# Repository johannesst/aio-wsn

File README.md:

# aio-wsn / FAIL
**Akustische Indoor-Ortung / Failed Audio Indoor Localisation**

Hard- und Softwareprojekt zur akustischen Ortung von Sensorknoten im Raum. Siehe dazu auch die [Projektpräsentation (PDF)](https://github.com/johannesst/aio-wsn/blob/master/doc/abschlusspr%C3%A4sentation/WSN%20Team%204%20AIO.pdf).

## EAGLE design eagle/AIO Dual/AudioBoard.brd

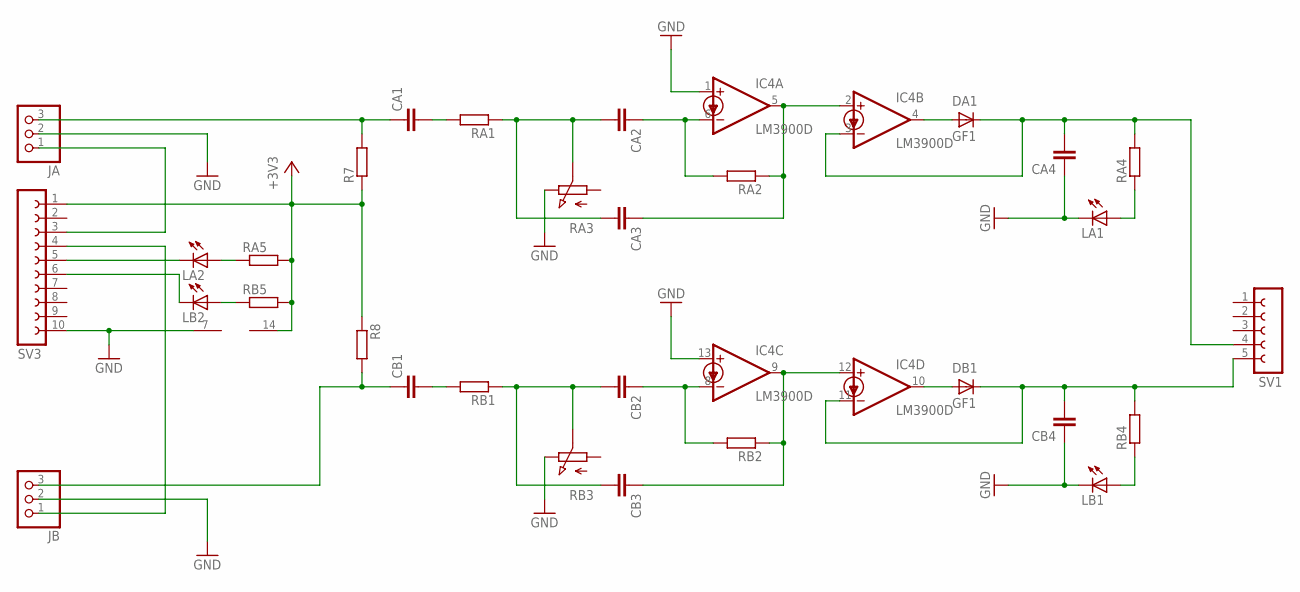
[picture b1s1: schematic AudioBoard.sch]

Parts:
CA1, CA2, CA3, CA4: C-EUC0402K; C0402K
CB1, CB2, CB3, CB4: C-EUC0402K; C0402K
DA1: GF1; SMA-DO214AC
DB1: GF1; SMA-DO214AC
IC4: LM3900D; SO14
JA: PINHD-1X3/90; 1X03/90
JB: PINHD-1X3/90; 1X03/90
LA1, LA2: LEDCHIPLED_0805; CHIPLED_0805
LB1, LB2: LEDCHIPLED_0805; CHIPLED_0805
R7, R8: R-EU_R0402; R0402
RA1, RA2, RA4, RA5: R-EU_R0402; R0402
RA3: PC25
RB1, RB2, RB4, RB5: R-EU_R0402; R0402
RB3: PC25
SV1: FE05-1
SV3: FE10-1; FE10

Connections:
+3V3: IC4.14 (V+), R7.1, R8.1, RA5.2, RB5.2, SV3.1
GND: CA4.1, CB4.1, IC4.1 (+IN), IC4.7 (GND), IC4.13 (+IN), JA.2, JB.2, LA1.C, LB1.C, RA3.E, RB3.E, SV3.10
unnamed: LA2.C, SV3.5
unnamed: LA2.A, RA5.1
unnamed: LB1.A, RB4.1
unnamed: JB.1, SV3.4
unnamed: CB2.1, IC4.8 (-IN), RB2.2
unnamed: CB3.1, IC4.9 (OUT), IC4.12 (+IN), RB2.1
unnamed: CB1.2, RB1.2
unnamed: JA.1, SV3.3
unnamed: CB1.1, JB.3, R8.2
unnamed: CB4.2, DB1.K (C), IC4.11 (-IN), RB4.2, SV1.5
unnamed: CB2.2, CB3.2, RB1.1, RB3.S
unnamed: DB1.A, IC4.10 (OUT)
unnamed: LB2.A, RB5.1
unnamed: CA1.1, JA.3, R7.2
unnamed: CA4.2, DA1.K (C), IC4.3 (-IN), RA4.2, SV1.4
unnamed: DA1.A, IC4.4 (OUT)
unnamed: CA2.2, CA3.2, RA1.1, RA3.S
unnamed: CA2.1, IC4.6 (-IN), RA2.2
unnamed: CA3.1, IC4.2 (+IN), IC4.5 (OUT), RA2.1
unnamed: CA1.2, RA1.2
unnamed: LB2.C, SV3.6
unnamed: LA1.A, RA4.1

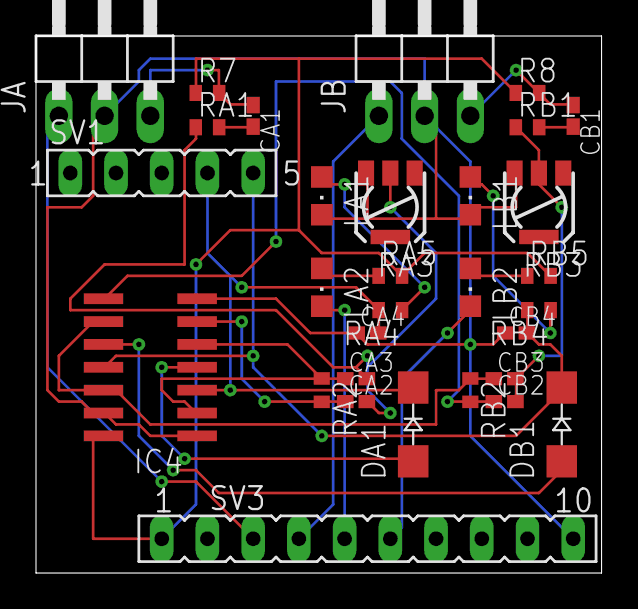
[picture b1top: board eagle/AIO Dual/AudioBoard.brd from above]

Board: 2 copper layers, 31.4 x 29.8 mm, 31 parts (0 on the bottom side), 24 nets.

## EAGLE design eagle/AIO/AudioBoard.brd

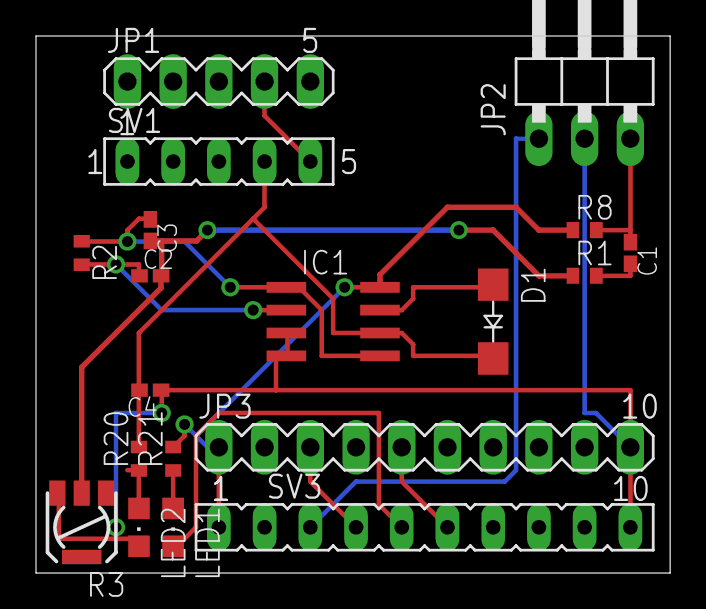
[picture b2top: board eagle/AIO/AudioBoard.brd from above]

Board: 2 copper layers, 35.2 x 29.8 mm, 19 parts (0 on the bottom side), 16 nets.

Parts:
C1, C2, C3, C4: C0402K
D1: GF1; SMA-DO214AC
IC1: LM4558D; SO08
JP1: MA05-1
JP2: 1X03/90
JP3: MA10-1
LED1, LED2: CHIPLED_0805
R1, R2, R8, R20, R21: R0402
R3: PC25
SV1: FE05-1
SV3: FE10

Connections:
+3V3: IC1.8, JP3.1, R8.1, R21.2, SV3.1
GND: C4.1, IC1.3, IC1.4, JP2.2, JP3.10, LED2.C, R3.E, SV3.10
unnamed: LED1.C, SV3.5
unnamed: LED1.A, R21.1
unnamed: LED2.A, R20.1
unnamed: JP3.5, SV3.6
unnamed: C2.2, C3.2, R1.1, R3.S
unnamed: C2.1, IC1.2, R2.2
unnamed: C3.1, IC1.1, IC1.5, R2.1
unnamed: C1.2, R1.2
unnamed: JP3.3, SV3.4
unnamed: C1.1, JP2.3, R8.2
unnamed: C4.2, D1.K, IC1.6, R20.2, SV1.4
unnamed: JP1.4, SV1.5
unnamed: D1.A, IC1.7
unnamed: JP2.1, SV3.3

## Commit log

2012-05-03 Initial gitignore
2012-05-03 initial working versions
2012-06-03 Added a test file.
2012-06-05 Added the LaTeX files for the first presentation.
2012-06-05 Added a test project that samples the analog-digital-converter and prints very little data.
2012-06-05 Ignored some binary files.
2012-06-05 Git rid of github default
2012-06-06 Started work on time sync
2012-06-06 Get rid of two unneccecary files
2012-06-06 First working (?) version of timesync
2012-06-06 Upadted Makefile
2012-06-06 Hopefully more useful debug output
2012-06-06 Notizen, kleinere Fixes.
2012-06-06 Added Zwischenpraesi to doc, but yet without meaningful content.
2012-06-07 Added Hardwarestuff to the presentation
2012-06-07 Added eagle files for INGA and AudioBoard.
2012-06-07 Small changes to the presentation.
2012-06-07 New graphic and some text enhancements in Zwischenpräsi.
2012-06-07 Fixed duplicate page.
2012-06-07 Jokes text has been included.
2012-07-19 Added missing files from long time ago
2012-07-21 Deleted unneeded files
2012-07-22 temporary save
2012-07-22 Implemnented software filtering via convolution and frequency detection.
2012-07-22 Added more specs
2012-07-22 Went back to 2kHz
2012-07-22 Commented and cleaned up.
2012-07-22 Last commit before I throw out that filter stuff again.
2012-07-22 Very basic timesync works
2012-07-22 Removed the inner loops and extremely shortened it by the way.
2012-07-22 temporary version
2012-07-22 Updated Makefile
2012-07-22 Most possibly messy version of this file.
2012-07-22 Bugfix in timesync first try
2012-07-23 Bugfix in timesync second try
2012-07-24 Great cleanup and restructuring. Changed my email address.
2012-07-24 Now features phase AND rare sync, common process, beeping, etc.
2012-07-25 Deleted two unused source files.
2012-07-25 Beep in eigenen Funktionen.
2012-07-25 Lauschen ist nun im timetry drin. Ob es genau funktioniert, muss man mal sehen.
2012-07-25 Moved some network stuff around, made sampling more efficient.
2012-07-25 Oppps, forgot to track those files.
2012-07-25 Fixed bugs.
2012-07-25 Fixed moar bugs.
2012-07-25 Preparing merge...
2012-07-25 Fixed merge conflict, implemented protocol changes for beep messages
2012-07-25 Removed files we don't need anymore
2012-07-25 Display routines added to the server.
2012-07-25 Timesync changed again
2012-07-25 cleanup
2012-07-25 Fixed syntax errors
2012-07-25 Fixed some errors and a lot of warnings.
2012-07-25 Added a patch for contiki, may version.
2012-07-25 Fixed bug in time_master
2012-07-25 More debug ouput for the neighbour list.
2012-07-25 Fixed memory problems with the list.
2012-07-26 Working on the table (currently disabled)
2012-07-26 prepare merge
2012-07-26 list fixes
2012-07-26 Table and debug output at the same time possible now.
2012-07-26 Old stuff that I forgot to commit before but goes me steadily on the nerven.
2012-07-26 test foo
2012-07-26 bugfix
2012-07-26 Dingenskirchen.
2012-07-26 Searched for errors, found nothing :(
2012-07-26 Fixed a severe bug that disabled all time sync, removed lots of debug printf.
2012-07-26 Master ist now acting as a slave to. Fixed some bugs, reworked networking, removed debug output
2012-07-26 This is a good version. Everything running smooth.
2012-07-26 This might be the final version
2012-07-26 Abschlusspräsentation first version
2012-07-26 Added pictures
2012-07-26 Now with screenshot
2012-07-26 Finalized presentation
2012-07-26 Switched two slides.
